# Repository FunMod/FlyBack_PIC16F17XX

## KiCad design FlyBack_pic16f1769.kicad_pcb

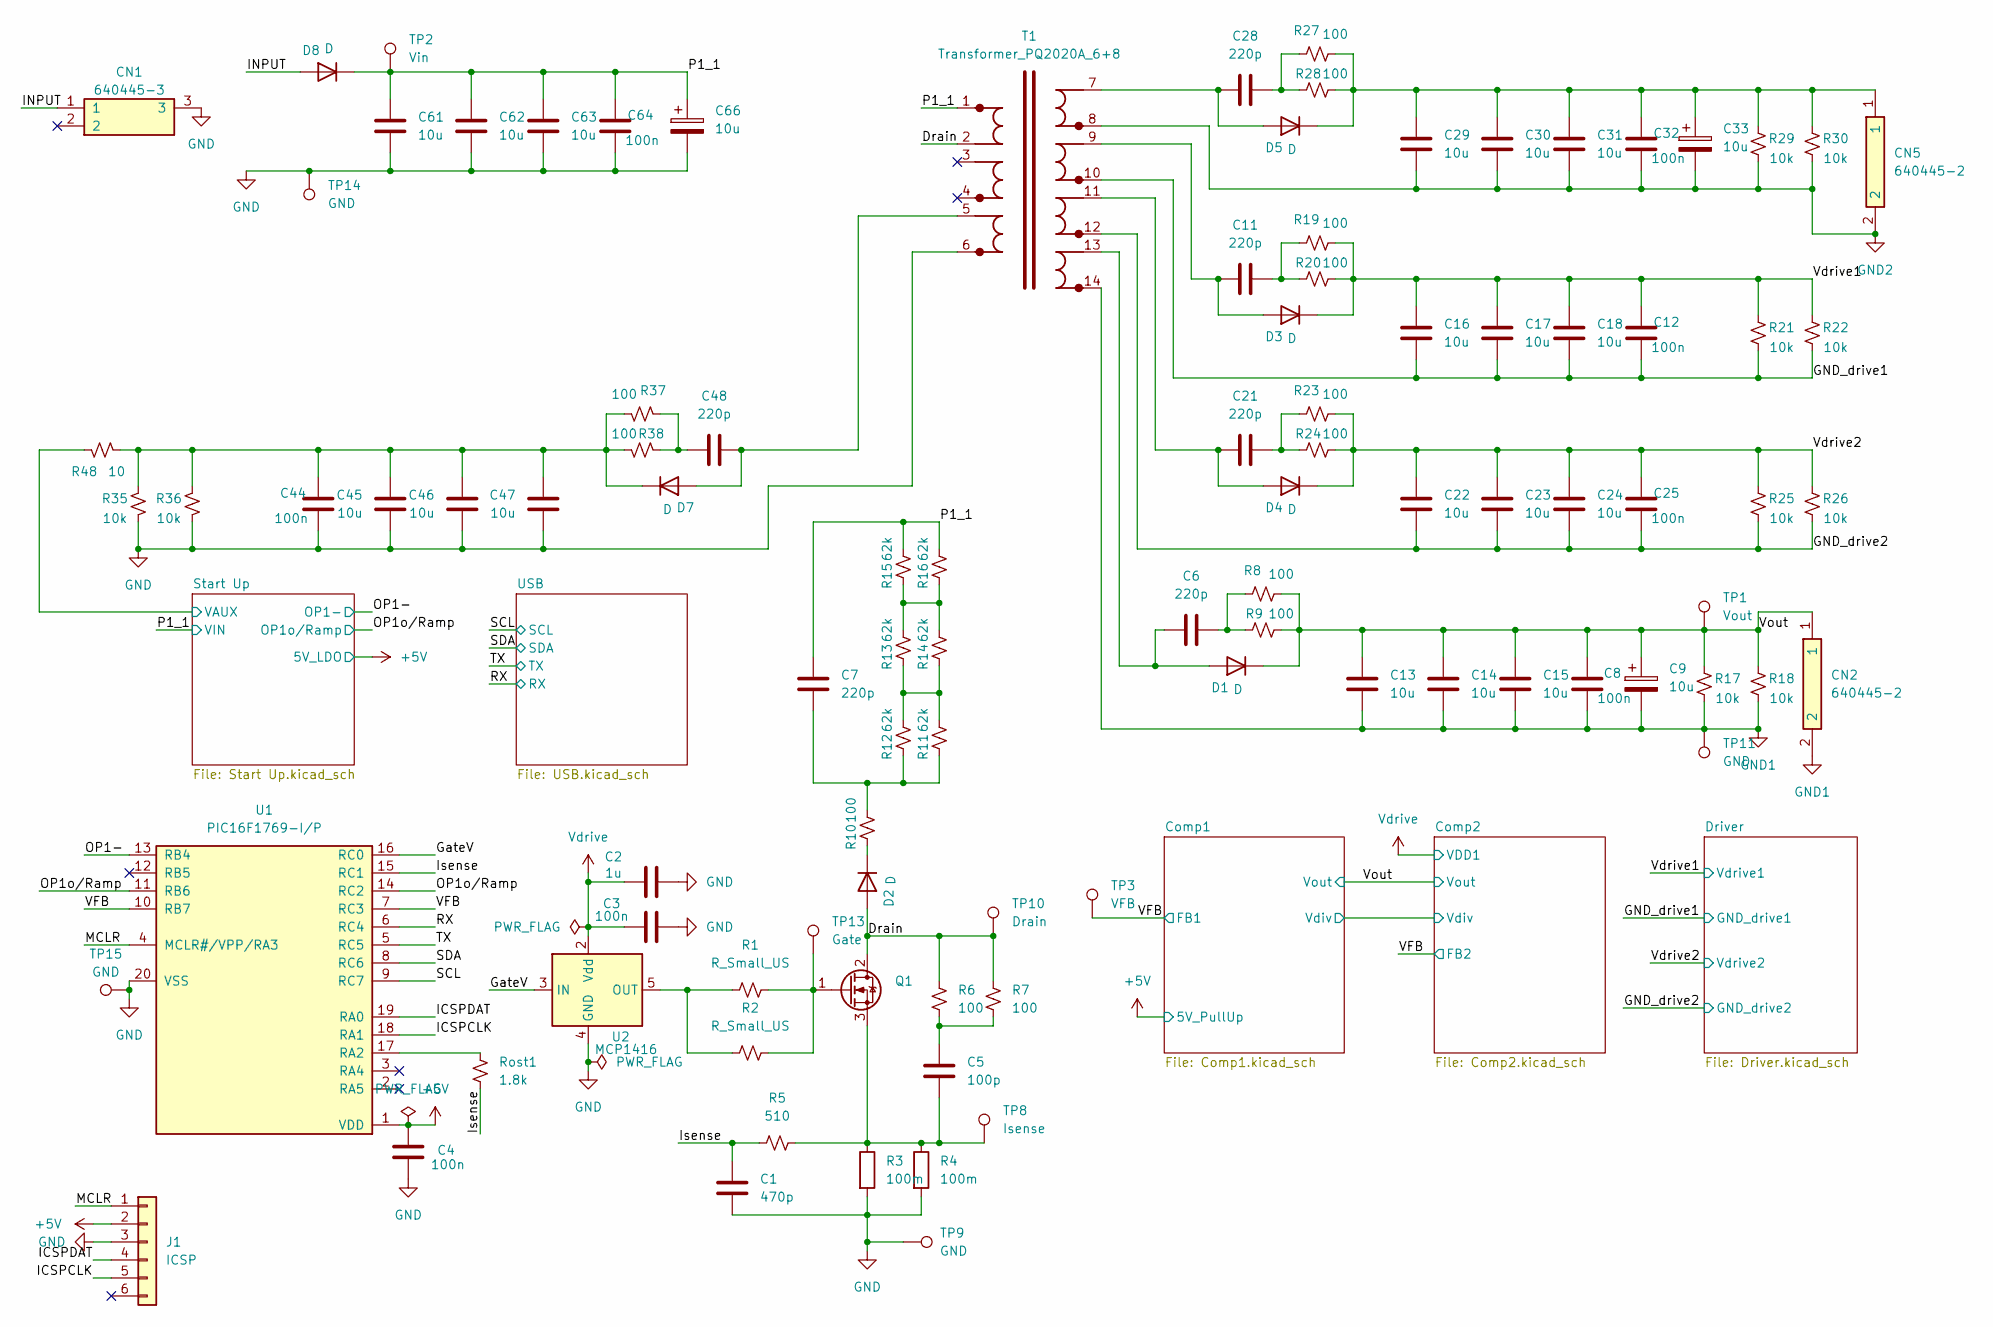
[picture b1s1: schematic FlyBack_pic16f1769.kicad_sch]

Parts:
C1: 470p; C_0603_1608Metric_Pad1.08x0.95mm_HandSolder
C2: 1u; C_0603_1608Metric_Pad1.08x0.95mm_HandSolder
C3, C4, C8, C12, C25, C32, C44, C64: 100n; C_0603_1608Metric_Pad1.08x0.95mm_HandSolder
C5: 100p; C_0805_2012Metric_Pad1.18x1.45mm_HandSolder
C6, C7, C11, C21, C28, C48: 220p; C_1206_3216Metric_Pad1.33x1.80mm_HandSolder
C9, C33, C66: 10u; CP_Elec_10x12.5
C13, C14, C15, C16, C17, C18, C22, C23, C24, C29, C30, C31, C45, C46, C47, C61, C62, C63: 10u; C_1206_3216Metric_Pad1.33x1.80mm_HandSolder
CN1: 640445-3; voltage_rating 600 V; MPN 640445-3
CN2, CN5: 640445-2; voltage_rating 600 V; MPN 640445-2
D1, D2, D3, D4, D5, D7: D; D_SMB_Handsoldering
D8: D; D_SMC
J1: ICSP; PinHeader_1x06_P2.54mm_Vertical
Q1: IPD50R380CE; TO-252-2
R1, R2: R_Small_US; R_0805_2012Metric_Pad1.20x1.40mm_HandSolder
R3, R4: 100m; R_2512_6332Metric_Pad1.40x3.35mm_HandSolder
R5: 510; R_0603_1608Metric_Pad0.98x0.95mm_HandSolder
R6, R7, R8, R9, R10, R19, R20, R23, R24, R27, R28, R37, R38: 100; R_1206_3216Metric_Pad1.30x1.75mm_HandSolder
R11, R12, R13, R14, R15, R16: 62k; R_1206_3216Metric_Pad1.30x1.75mm_HandSolder
R17, R18, R21, R22, R25, R26, R29, R30, R35, R36: 10k; R_1206_3216Metric_Pad1.30x1.75mm_HandSolder
R48: 10; R_1206_3216Metric_Pad1.30x1.75mm_HandSolder
Rost1: 1.8k; R_0603_1608Metric_Pad0.98x0.95mm_HandSolder
T1: Transformer_PQ2020A_6+8; Transformer_PQ2020A_6+8_23x23mm
TP1: Vout; TestPoint_Keystone_5005-5009_Compact
TP2: Vin; TestPoint_Keystone_5005-5009_Compact
TP3: VFB; TestPoint_Keystone_5005-5009_Compact
TP8: Isense; TestPoint_Keystone_5005-5009_Compact
TP9, TP11, TP14, TP15: GND; TestPoint_Keystone_5005-5009_Compact
TP10: Drain; TestPoint_Keystone_5005-5009_Compact
TP13: Gate; TestPoint_Keystone_5005-5009_Compact
U1: PIC16F1769-I/P; PIC16F1769-I_P; voltage 2.3 V; MPN PIC16F1769-I/P
U2: MCP1416; SOT-23-5_HandSoldering

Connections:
+5V: C4.2, J1.2, U1.1 (VDD); also elsewhere on the board
/Drain: D2.2 (A), Q1.2 (D), R6.1, R7.1, T1.2, TP10.1 (1_1)
/GND_drive1: C12.1, C16.1, C17.1, C18.1, R21.1, R22.1, T1.10; also elsewhere on the board
/GND_drive2: C22.1, C23.1, C24.1, C25.1, R25.1, R26.1, T1.12; also elsewhere on the board
/GateV: U1.16 (RC0), U2.3 (IN)
/ICSPCLK: J1.5, U1.18 (RA1)
/ICSPDAT: J1.4, U1.19 (RA0)
/INPUT: CN1.1, D8.2 (A)
/Isense: C1.1, R5.1, Rost1.1, U1.15 (RC1)
/MCLR: J1.1, U1.4 (MCLR#/VPP/RA3)
/OP1-: U1.13 (RB4); also elsewhere on the board
/OP1o/Ramp: U1.11 (RB6), U1.14 (RC2); also elsewhere on the board
/P1_1: C7.2, C61.2, C62.2, C63.2, C64.2, C66.1, D8.1 (K), R15.2, R16.2, T1.1, TP2.1 (1_1); also elsewhere on the board
/RX: U1.6 (RC4); also elsewhere on the board
/SCL: U1.9 (RC7); also elsewhere on the board
/SDA: U1.8 (RC6); also elsewhere on the board
/Start Up/VAUX: R48.2; also elsewhere on the board
/TX: U1.5 (RC5); also elsewhere on the board
/VFB: TP3.1 (1_1), U1.7 (RC3), U1.10 (RB7); also elsewhere on the board
/Vdrive1: C12.2, C16.2, C17.2, C18.2, D3.1 (K), R19.2, R20.2, R21.2, R22.2; also elsewhere on the board
/Vdrive2: C22.2, C23.2, C24.2, C25.2, D4.1 (K), R23.2, R24.2, R25.2, R26.2; also elsewhere on the board
/Vout: C8.2, C9.1, C13.2, C14.2, C15.2, CN2.1, D1.1 (K), R8.2, R9.2, R17.2, R18.2, TP1.1 (1_1); also elsewhere on the board
GND: C1.2, C2.2, C3.2, C4.1, C44.1, C45.1, C46.1, C47.1, C61.1, C62.1, C63.1, C64.1, C66.2, CN1.3, J1.3, R3.2, R4.2, R35.1, R36.1, T1.6, TP9.1 (1_1), TP14.1 (1_1), TP15.1 (1_1), U1.20 (VSS), U2.4 (GND); also elsewhere on the board
GND1: C8.1, C9.2, C13.1, C14.1, C15.1, CN2.2, R17.1, R18.1, T1.14, TP11.1 (1_1); also elsewhere on the board
GND2: C29.1, C30.1, C31.1, C32.1, C33.2, CN5.2, R29.1, R30.1, T1.8
unnamed: C5.1, R6.2, R7.2
unnamed: C6.2, R8.1, R9.1
unnamed: C7.1, R10.2, R11.1, R12.1
unnamed: C11.2, R19.1, R20.1
unnamed: C21.2, R23.1, R24.1
unnamed: C28.2, R27.1, R28.1
unnamed: C48.2, R37.1, R38.1
unnamed: C6.1, D1.2 (A), T1.13
unnamed: D2.1 (K), R10.1
unnamed: C11.1, D3.2 (A), T1.9
unnamed: C21.1, D4.2 (A), T1.11
unnamed: C28.1, D5.2 (A), T1.7
unnamed: C29.2, C30.2, C31.2, C32.2, C33.1, CN5.1, D5.1 (K), R27.2, R28.2, R29.2, R30.2
unnamed: C48.1, D7.2 (A), T1.5
unnamed: C44.2, C45.2, C46.2, C47.2, D7.1 (K), R35.2, R36.2, R37.2, R38.2, R48.1
unnamed: Q1.1 (G), R1.2, R2.2, TP13.1 (1_1)
unnamed: C5.2, Q1.3 (S), R3.1, R4.1, R5.2, TP8.1 (1_1)
unnamed: R11.2, R12.2, R13.1, R14.1
unnamed: R13.2, R14.2, R15.1, R16.1
unnamed: Rost1.2, U1.17 (RA2)
unnamed: R1.1, R2.1, U2.5 (OUT)
Vdrive: C2.1, C3.1, U2.2 (Vdd); also elsewhere on the board

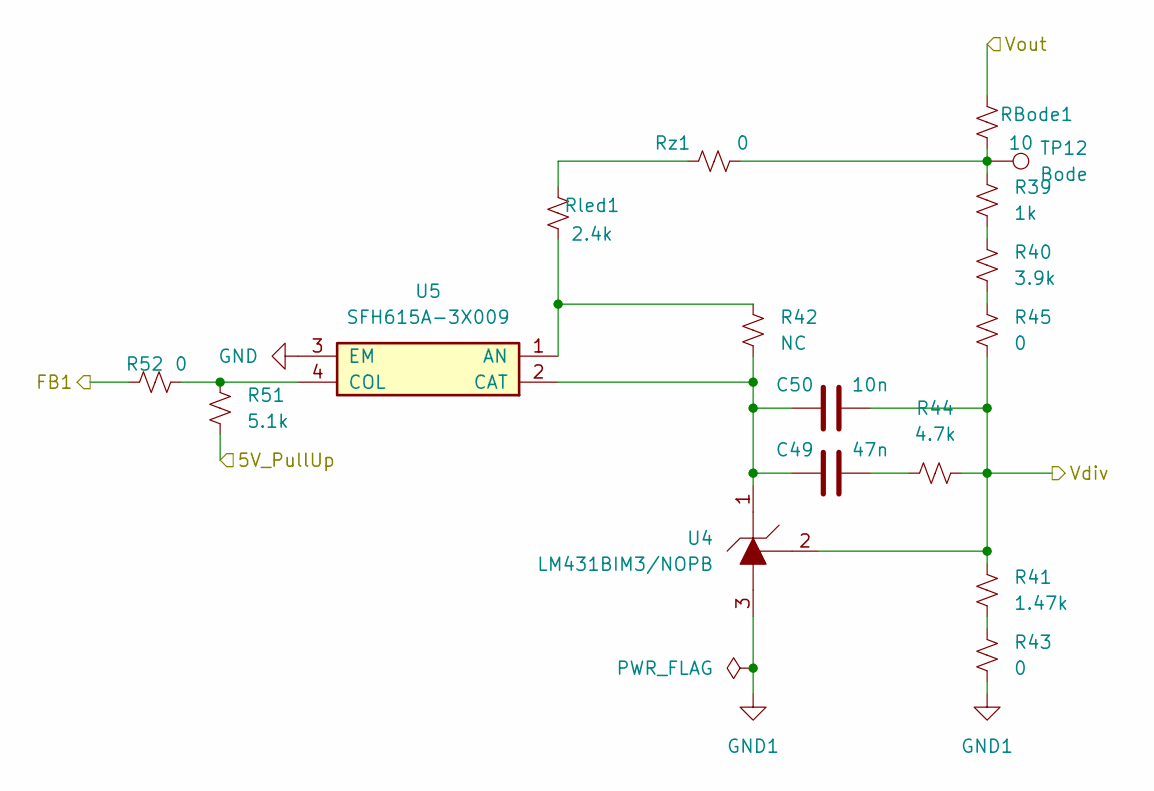
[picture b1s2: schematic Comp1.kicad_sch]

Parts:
C49: 47n; C_0603_1608Metric_Pad1.08x0.95mm_HandSolder
C50: 10n; C_0603_1608Metric_Pad1.08x0.95mm_HandSolder
R39: 1k; R_0603_1608Metric_Pad0.98x0.95mm_HandSolder
R40: 3.9k; R_0603_1608Metric_Pad0.98x0.95mm_HandSolder
R41: 1.47k; R_0603_1608Metric_Pad0.98x0.95mm_HandSolder
R42: NC; R_0603_1608Metric_Pad0.98x0.95mm_HandSolder
R43, R45, R52: 0; R_0603_1608Metric_Pad0.98x0.95mm_HandSolder
R44: 4.7k; R_0603_1608Metric_Pad0.98x0.95mm_HandSolder
R51: 5.1k; R_0603_1608Metric_Pad0.98x0.95mm_HandSolder
RBode1: 10; R_1206_3216Metric_Pad1.30x1.75mm_HandSolder
Rled1: 2.4k; R_1206_3216Metric_Pad1.30x1.75mm_HandSolder
Rz1: 0; R_1206_3216Metric_Pad1.30x1.75mm_HandSolder
TP12: Bode; TestPoint_Keystone_5005-5009_Compact
U4: LM431BIM3/NOPB; LM431BIM3_NOPB; tolerance 1 %; MPN LM431BIM3/NOPB
U5: SFH615A-3X009; MPN SFH615A-3X009

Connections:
+5V: R51.1; also elsewhere on the board
/Comp1/Vdiv: C50.1, R41.2, R44.1, R45.1, U4.2 (Reference); also elsewhere on the board
/VFB: R52.2; also elsewhere on the board
/Vout: RBode1.2; also elsewhere on the board
GND: U5.3 (EM); also elsewhere on the board
GND1: R43.1, U4.3 (Anode); also elsewhere on the board
unnamed: C49.1, R44.2
unnamed: R39.1, R40.2
unnamed: R39.2, RBode1.1, Rz1.1, TP12.1 (1_1)
unnamed: R40.1, R45.2
unnamed: R41.1, R43.2
unnamed: Rled1.2, Rz1.2
unnamed: C49.2, C50.2, R42.1, U4.1 (Cathode), U5.2 (CAT)
unnamed: R42.2, Rled1.1, U5.1 (AN)
unnamed: R51.2, R52.1, U5.4 (COL)

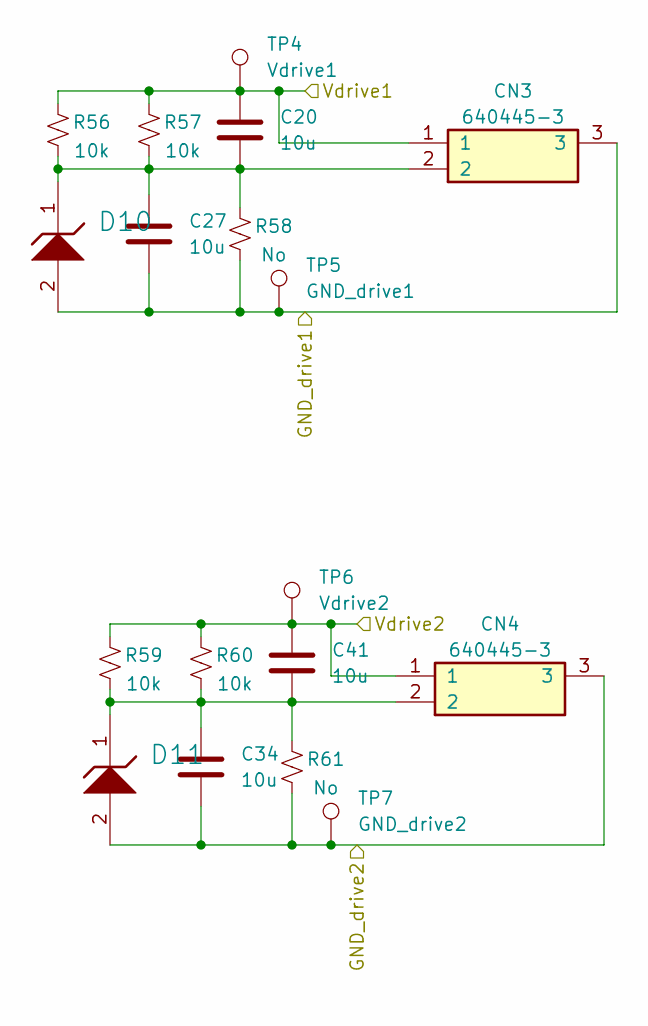
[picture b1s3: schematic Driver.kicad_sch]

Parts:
C20, C27, C34, C41: 10u; C_1206_3216Metric_Pad1.33x1.80mm_HandSolder
CN3, CN4: 640445-3; voltage_rating 600 V; MPN 640445-3
D10, D11: MMSZ5226BT1G; tolerance 5 %; voltage_rating 3.3 V; MPN MMSZ5226BT1G
R56, R57, R59, R60: 10k; R_1206_3216Metric_Pad1.30x1.75mm_HandSolder
R58, R61: No; R_1206_3216Metric_Pad1.30x1.75mm_HandSolder
TP4: Vdrive1; TestPoint_Keystone_5005-5009_Compact
TP5: GND_drive1; TestPoint_Keystone_5005-5009_Compact
TP6: Vdrive2; TestPoint_Keystone_5005-5009_Compact
TP7: GND_drive2; TestPoint_Keystone_5005-5009_Compact

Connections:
/GND_drive1: C27.1, CN3.3, D10.2 (A), R58.1, TP5.1 (1_1); also elsewhere on the board
/GND_drive2: C34.1, CN4.3, D11.2 (A), R61.1, TP7.1 (1_1); also elsewhere on the board
/Vdrive1: C20.2, CN3.1, R56.2, R57.2, TP4.1 (1_1); also elsewhere on the board
/Vdrive2: C41.2, CN4.1, R59.2, R60.2, TP6.1 (1_1); also elsewhere on the board
unnamed: C20.1, C27.2, CN3.2, D10.1 (K), R56.1, R57.1, R58.2
unnamed: C34.2, C41.1, CN4.2, D11.1 (K), R59.1, R60.1, R61.2

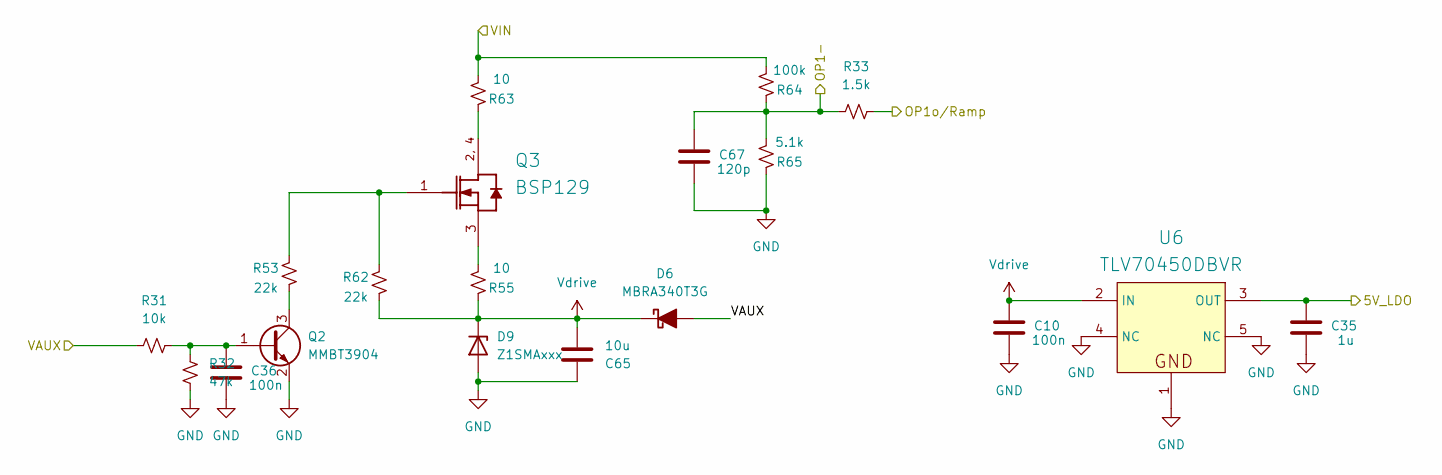
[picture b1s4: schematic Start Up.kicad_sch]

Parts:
C10, C36: 100n; C_0603_1608Metric_Pad1.08x0.95mm_HandSolder
C35: 1u; C_0603_1608Metric_Pad1.08x0.95mm_HandSolder
C65: 10u; C_1206_3216Metric_Pad1.33x1.80mm_HandSolder
C67: 120p; C_0603_1608Metric_Pad1.08x0.95mm_HandSolder
D6: MBRA340T3G; voltage_rating 40 V; MPN MBRA340T3G
D9: Z1SMAxxx; D_SMA
Q2: MMBT3904; SOT-23
Q3: BSP129; MPN BSP129
R31: 10k; R_0603_1608Metric_Pad0.98x0.95mm_HandSolder
R32: 47k; R_0603_1608Metric_Pad0.98x0.95mm_HandSolder
R33: 1.5k; R_0603_1608Metric_Pad0.98x0.95mm_HandSolder
R53, R62: 22k; R_1206_3216Metric_Pad1.30x1.75mm_HandSolder
R55, R63: 10; R_1206_3216Metric_Pad1.30x1.75mm_HandSolder
R64: 100k; R_1206_3216Metric_Pad1.30x1.75mm_HandSolder
R65: 5.1k; R_0805_2012Metric_Pad1.20x1.40mm_HandSolder
U6: TLV70450DBVR; MPN TLV70450DBVR

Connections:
+5V: C35.2, U6.3 (OUT); also elsewhere on the board
/OP1-: C67.2, R33.2, R64.2, R65.1; also elsewhere on the board
/OP1o/Ramp: R33.1; also elsewhere on the board
/P1_1: R63.1, R64.1; also elsewhere on the board
/Start Up/VAUX: D6.2 (A), R31.1; also elsewhere on the board
GND: C10.1, C35.1, C36.1, C65.2, C67.1, D9.2 (A), Q2.2 (E), R32.1, R65.2, U6.1 (GND), U6.4 (NC), U6.5 (NC); also elsewhere on the board
unnamed: C36.2, Q2.1 (B), R31.2, R32.2
unnamed: Q2.3 (C), R53.1
unnamed: Q3.2 (DRAIN), Q3.4 (DRAIN), R63.2
unnamed: Q3.1 (GATE), R53.2, R62.2
unnamed: Q3.3 (SOURCE), R55.1
Vdrive: C10.2, C65.1, D6.1 (K), D9.1 (K), R55.2, R62.1, U6.2 (IN); also elsewhere on the board

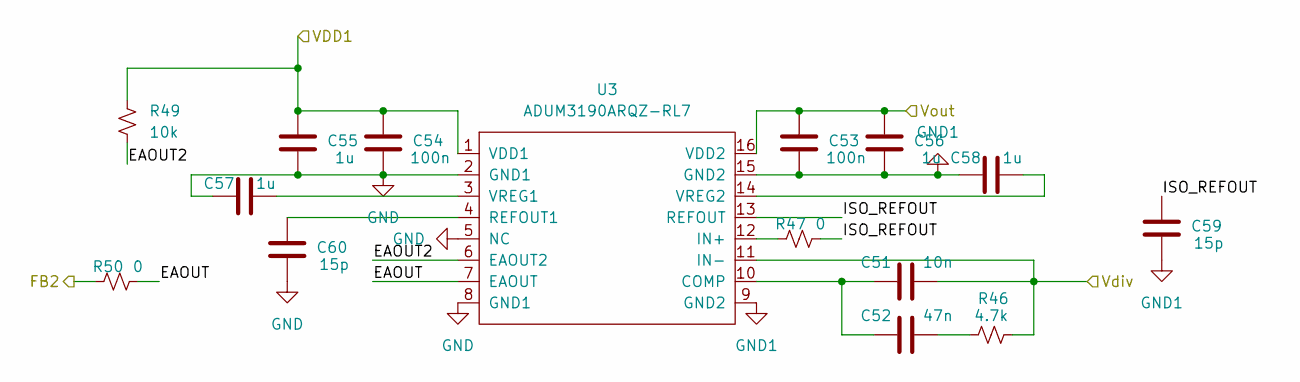
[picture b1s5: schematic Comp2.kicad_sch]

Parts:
C51: 10n; C_0603_1608Metric_Pad1.08x0.95mm_HandSolder
C52: 47n; C_0603_1608Metric_Pad1.08x0.95mm_HandSolder
C53, C54: 100n; C_0603_1608Metric_Pad1.08x0.95mm_HandSolder
C55, C56, C57, C58: 1u; C_0603_1608Metric_Pad1.08x0.95mm_HandSolder
C59, C60: 15p; C_0603_1608Metric_Pad1.08x0.95mm_HandSolder
R46: 4.7k; R_0603_1608Metric_Pad0.98x0.95mm_HandSolder
R47: 0; R_0402_1005Metric_Pad0.72x0.64mm_HandSolder
R49: 10k; R_0603_1608Metric_Pad0.98x0.95mm_HandSolder
R50: 0; R_0603_1608Metric_Pad0.98x0.95mm_HandSolder
U3: ADUM3190ARQZ-RL7; MPN ADUM3190ARQZ-RL7

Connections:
/Comp1/Vdiv: C51.1, R46.1, U3.11 (IN-); also elsewhere on the board
/Comp2/EAOUT: R50.1, U3.7 (EAOUT)
/Comp2/EAOUT2: R49.1, U3.6 (EAOUT2)
/Comp2/ISO_REFOUT: C59.2, R47.1, U3.13 (REFOUT)
/VFB: R50.2; also elsewhere on the board
/Vout: C53.2, C56.2, U3.16 (VDD2); also elsewhere on the board
GND: C54.1, C55.1, C57.2, C60.1, U3.2 (GND1), U3.5 (NC), U3.8 (GND1); also elsewhere on the board
GND1: C53.1, C56.1, C58.2, C59.1, U3.9 (GND2), U3.15 (GND2); also elsewhere on the board
unnamed: C52.1, R46.2
unnamed: C51.2, C52.2, U3.10 (COMP)
unnamed: R47.2, U3.12 (IN+)
unnamed: C60.2, U3.4 (REFOUT1)
unnamed: C57.1, U3.3 (VREG1)
unnamed: C58.1, U3.14 (VREG2)
Vdrive: C54.2, C55.2, R49.2, U3.1 (VDD1); also elsewhere on the board

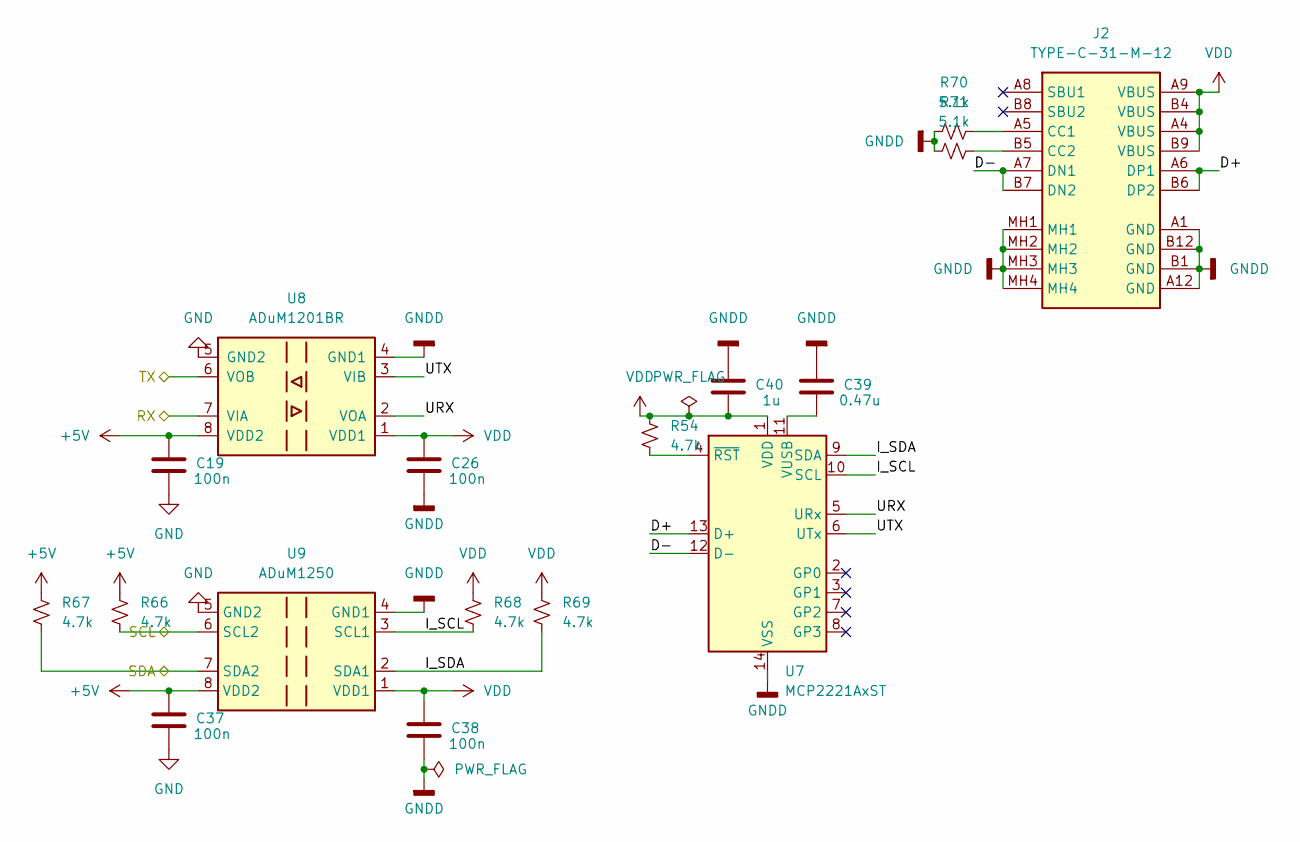
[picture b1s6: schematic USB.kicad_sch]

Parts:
C19, C26, C37, C38: 100n; C_0603_1608Metric_Pad1.08x0.95mm_HandSolder
C39: 0.47u; C_0603_1608Metric_Pad1.08x0.95mm_HandSolder
C40: 1u; C_0603_1608Metric_Pad1.08x0.95mm_HandSolder
J2: TYPE-C-31-M-12; MPN TYPE-C-31-M-12
R54, R66, R67, R68, R69: 4.7k; R_0603_1608Metric_Pad0.98x0.95mm_HandSolder
R70, R71: 5.1k; R_0603_1608Metric_Pad0.98x0.95mm_HandSolder
U7: MCP2221AxST; TSSOP-14_4.4x5mm_P0.65mm
U8: ADuM1201BR; SOIC-8_3.9x4.9mm_P1.27mm
U9: ADuM1250; SOIC-8_3.9x4.9mm_P1.27mm

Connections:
+5V: C19.2, C37.2, R66.2, R67.2, U8.8 (VDD2), U9.8 (VDD2); also elsewhere on the board
/RX: U8.7 (VIA); also elsewhere on the board
/SCL: R66.1, U9.6 (SCL2); also elsewhere on the board
/SDA: R67.1, U9.7 (SDA2); also elsewhere on the board
/TX: U8.6 (VOB); also elsewhere on the board
/USB/D+: J2.A6 (DP1), J2.B6 (DP2), U7.13 (D+)
/USB/D-: J2.A7 (DN1), J2.B7 (DN2), U7.12 (D-)
/USB/I_SCL: R68.1, U7.10 (SCL), U9.3 (SCL1)
/USB/I_SDA: R69.1, U7.9 (SDA), U9.2 (SDA1)
/USB/URX: U7.5 (URx), U8.2 (VOA)
/USB/UTX: U7.6 (UTx), U8.3 (VIB)
GND: C19.1, C37.1, U8.5 (GND2), U9.5 (GND2); also elsewhere on the board
GNDD: C26.1, C38.1, C39.2, C40.2, J2.A1 (GND), J2.A12 (GND), J2.B1 (GND), J2.B12 (GND), J2.MH1, J2.MH2, J2.MH3, J2.MH4, R70.1, R71.1, U7.14 (VSS), U8.4 (GND1), U9.4 (GND1)
unnamed: J2.A5 (CC1), R70.2
unnamed: J2.B5 (CC2), R71.2
unnamed: C39.1, U7.11 (VUSB)
unnamed: R54.1, U7.4 (~RST)
VDD: C26.2, C38.2, C40.1, J2.A4 (VBUS), J2.A9 (VBUS), J2.B4 (VBUS), J2.B9 (VBUS), R54.2, R68.2, R69.2, U7.1 (VDD), U8.1 (VDD1), U9.1 (VDD1)

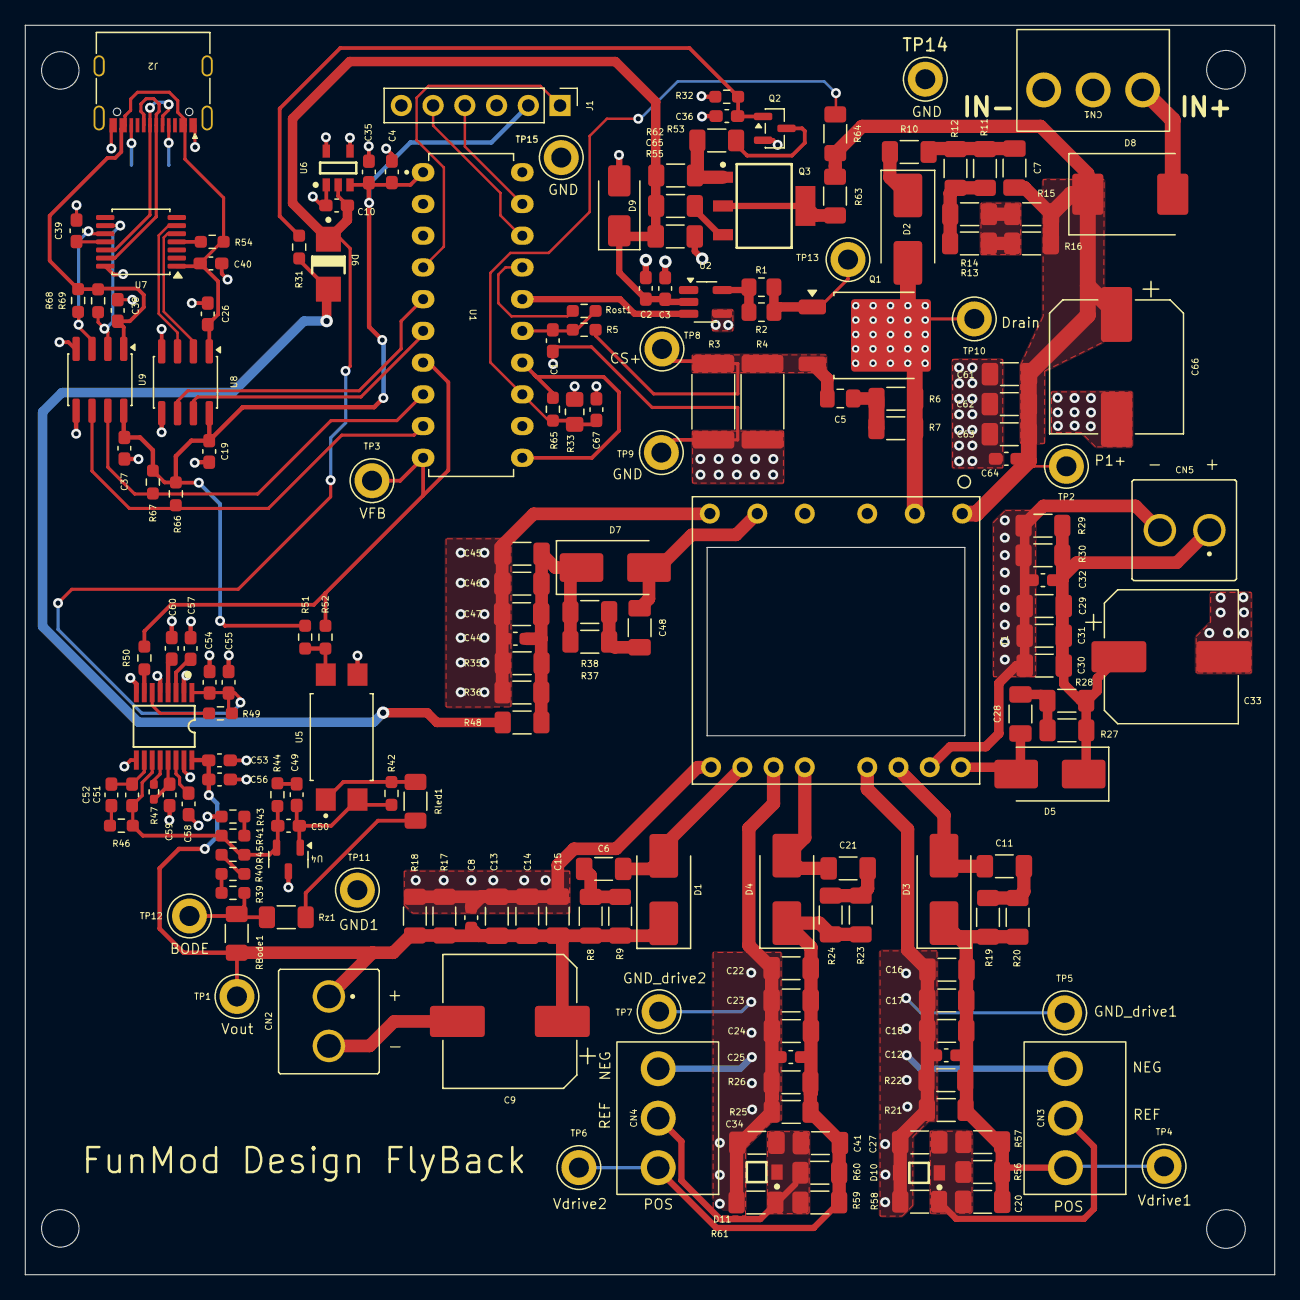
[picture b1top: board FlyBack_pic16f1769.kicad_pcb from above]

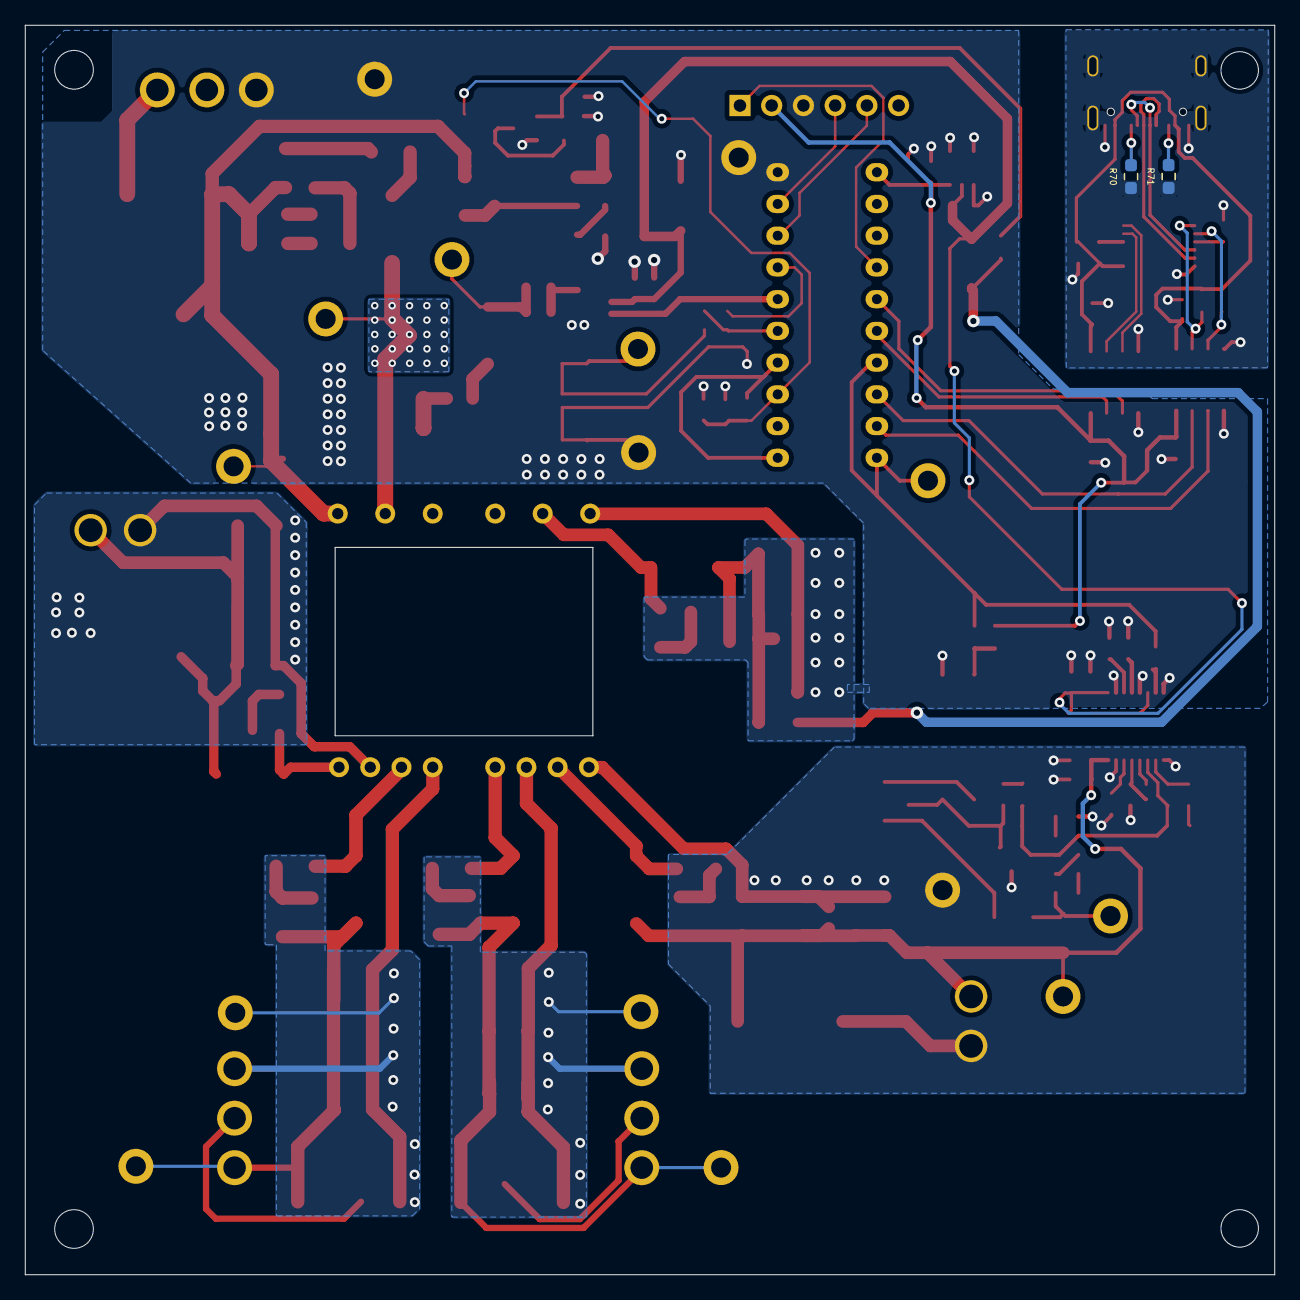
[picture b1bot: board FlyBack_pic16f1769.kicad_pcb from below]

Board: 2 copper layers, 100.0 x 100.0 mm, 185 parts (2 on the bottom side), 85 nets.
